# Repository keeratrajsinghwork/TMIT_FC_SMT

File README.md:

# TMIT_FC_SMT
 SMT based flight computer created for thrustMIT

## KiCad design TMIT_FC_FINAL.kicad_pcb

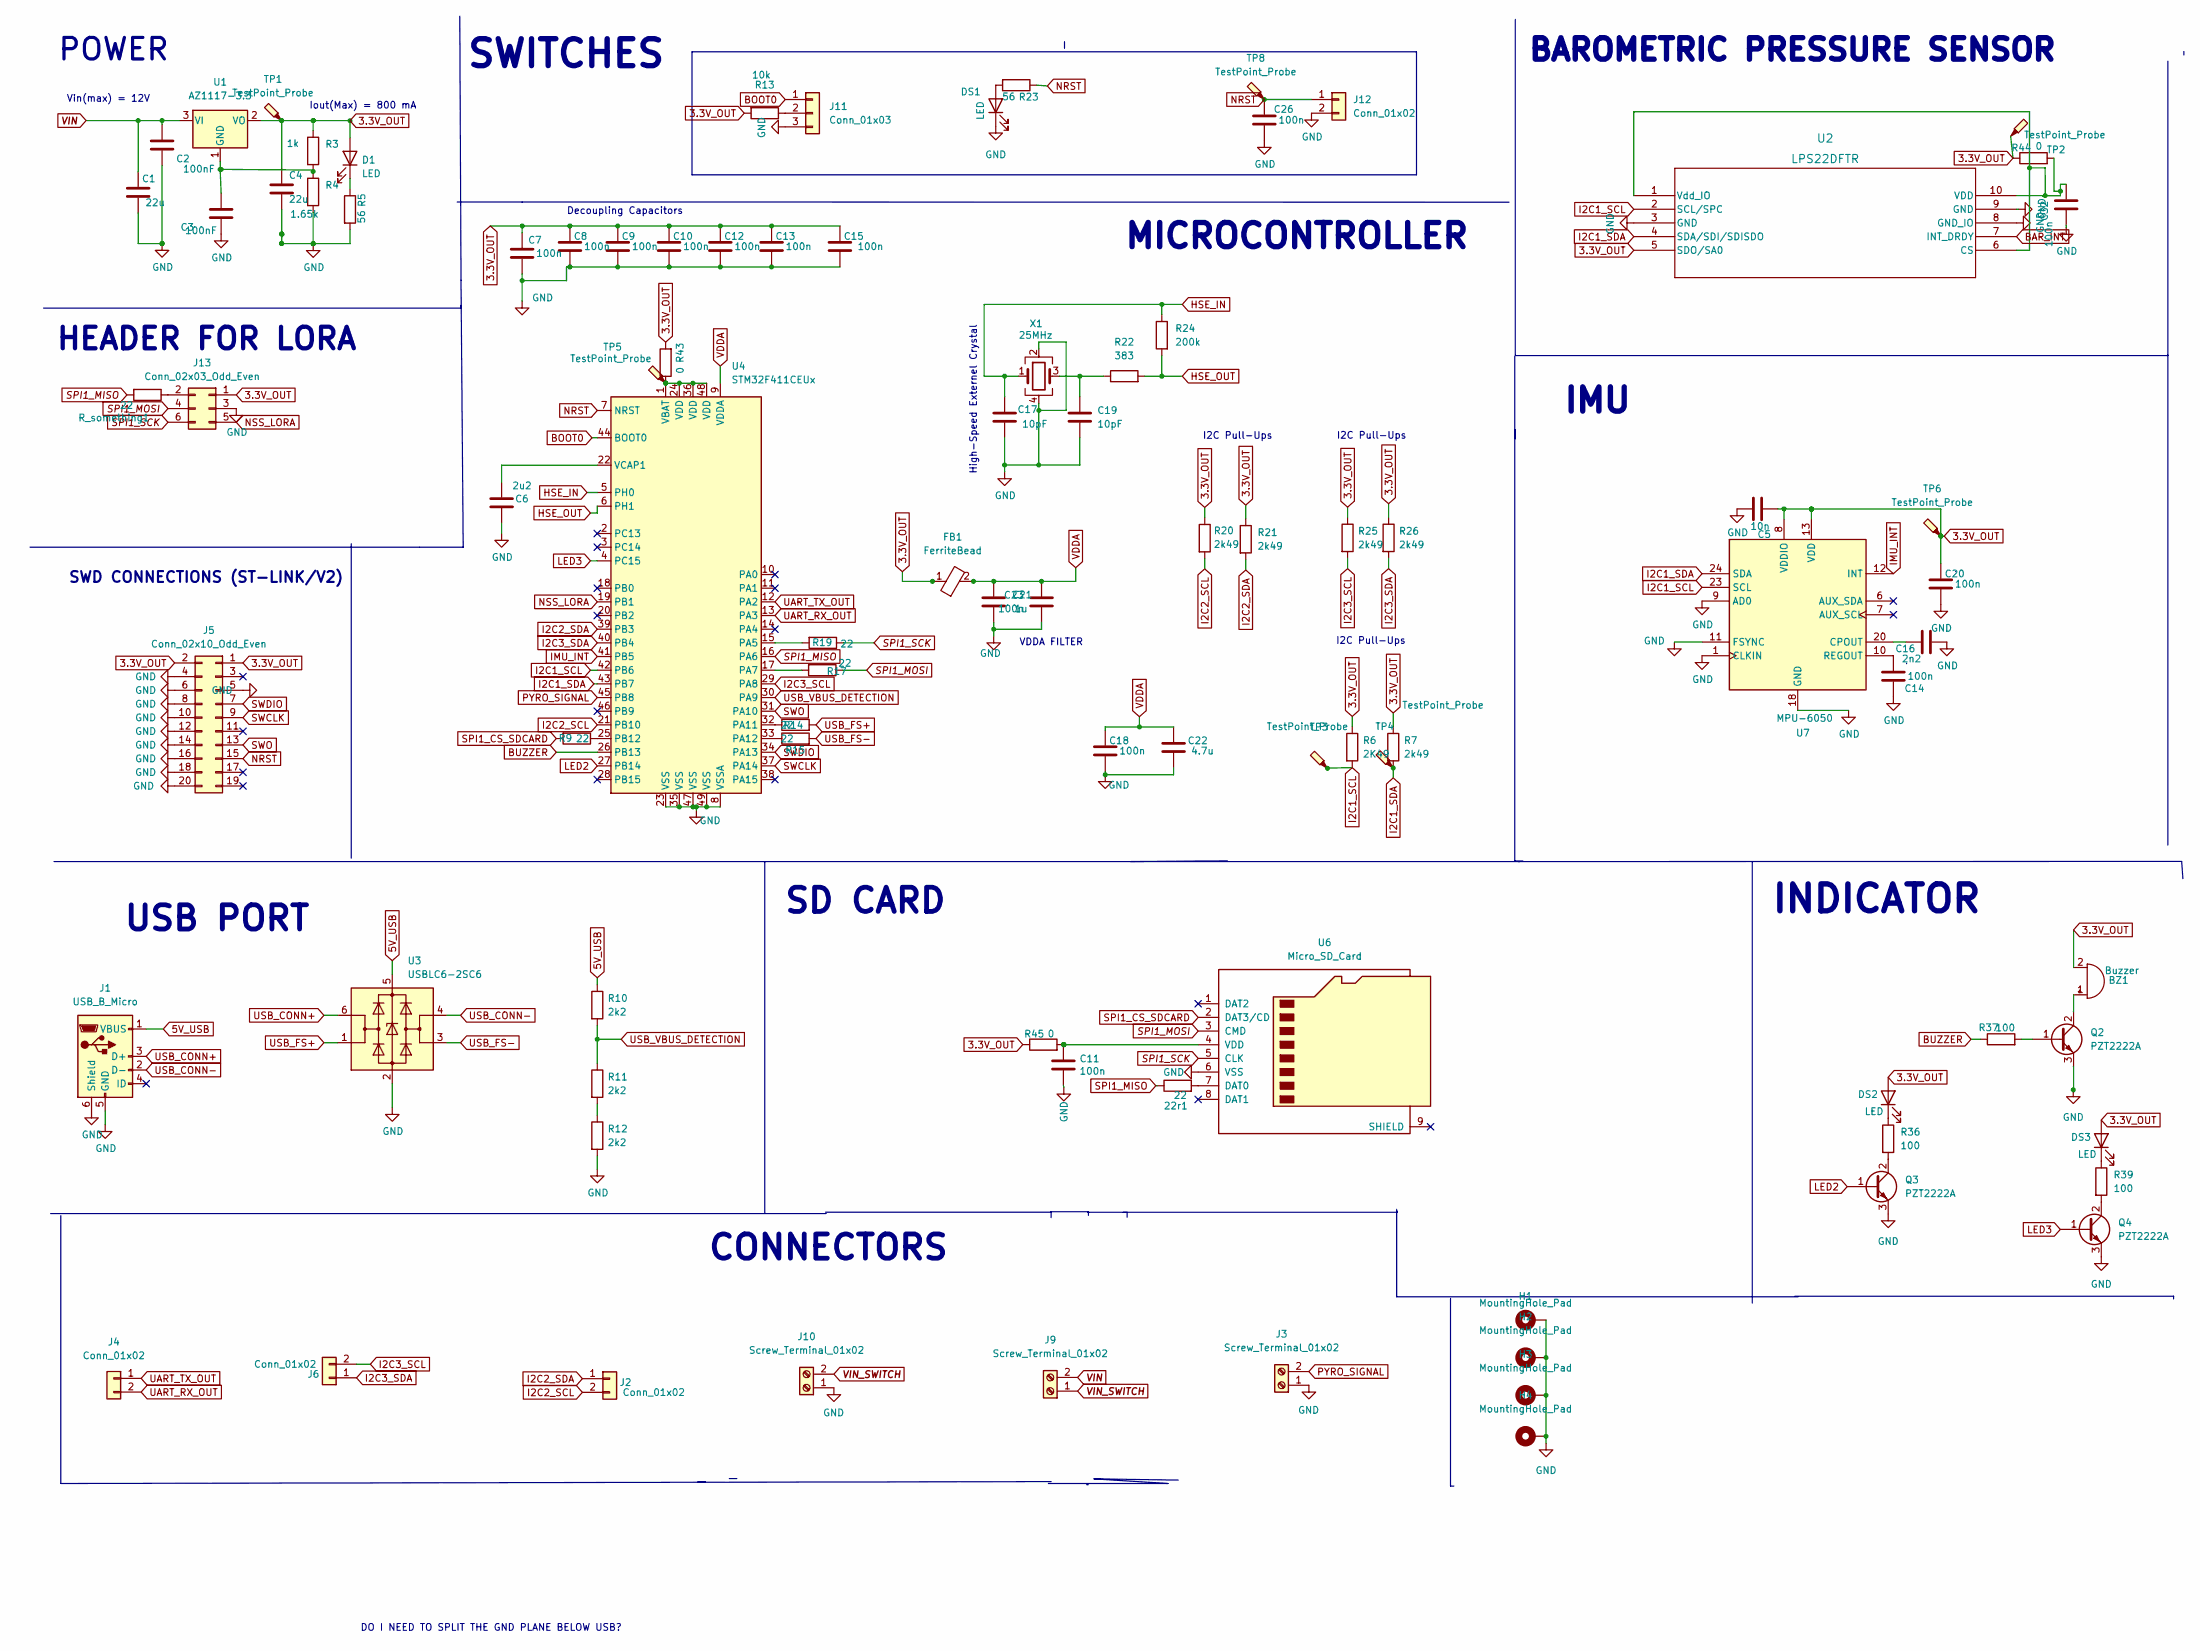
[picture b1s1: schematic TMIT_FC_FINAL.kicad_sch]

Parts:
22r1: 22; R_0603_1608Metric
BZ1: Buzzer; PinHeader_1x02_P2.54mm_Vertical
C1, C4: 22u; C_1206_3216Metric
C2, C3: 100nF; C_1206_3216Metric
C5: 10n; C_0805_2012Metric
C6: 2u2; C_1206_3216Metric
C7, C8, C9, C10, C11, C12, C13, C15, C18, C23, C26, C32: 100n; C_1206_3216Metric
C14, C20: 100n; C_0603_1608Metric
C16: 2n2; C_0805_2012Metric
C17, C19: 10pF; C_1206_3216Metric
C21: 1u; C_1206_3216Metric
C22: 4.7u; C_1206_3216Metric
D1: LED; LED_0805_2012Metric
DS1, DS2, DS3: LED; LED_0805_2012Metric
FB1: FerriteBead; L_0805_2012Metric
H1, H2, H3, H4: MountingHole_Pad; MountingHole_3.2mm_M3_Pad
J1: USB_B_Micro; USB_Micro-B_Molex-105133-0001
J2, J4, J6, J12: Conn_01x02; TerminalBlock_bornier-2_P5.08mm
J3, J9, J10: Screw_Terminal_01x02; TerminalBlock_bornier-2_P5.08mm
J5: Conn_02x10_Odd_Even; PinHeader_2x10_P2.54mm_Vertical
J11: Conn_01x03; TerminalBlock_bornier-3_P5.08mm
J13: Conn_02x03_Odd_Even; PinSocket_2x03_P2.54mm_Vertical
Q2, Q3, Q4: PZT2222A; SOT-223-3_TabPin2
R3: 1k; R_1206_3216Metric
R4: 1.65k; R_1206_3216Metric
R5, R23: 56; R_1206_3216Metric
R6: 2K49; R_1206_3216Metric
R7, R20, R21, R25, R26: 2k49; R_1206_3216Metric
R9, R14, R15, R17, R19: 22; R_1206_3216Metric
R10, R11, R12: 2k2; R_1206_3216Metric
R13: 10k; R_1206_3216Metric
R22: 383; R_1206_3216Metric
R24: 200k; R_1206_3216Metric
R36, R37, R39: 100; R_1206_3216Metric
R43, R44, R45: 0; R_1206_3216Metric
R_something1: 22; R_0603_1608Metric
TP1, TP2, TP3, TP4, TP5, TP6, TP8: TestPoint_Probe; TestPoint_Pad_2.0x2.0mm
U1: AZ1117-3.3; SOT-223-3_TabPin2
U2: LPS22DFTR; QFN_22DFTR_STM
U3: USBLC6-2SC6; SOT-23-6
U4: STM32F411CEUx; QFN-48-1EP_7x7mm_P0.5mm_EP5.6x5.6mm
U6: Micro_SD_Card; Micro_SD
U7: MPU-6050; InvenSense_QFN-24_4x4mm_P0.5mm
X1: 25MHz; Crystal_SMD_Abracon_ABM8G-4Pin_3.2x2.5mm

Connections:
3.3V_OUT: BZ1.2 (+), C4.1, C5.2, C7.1, C8.1, C9.1, C10.1, C12.1, C13.1, C15.1, C20.1, D1.2 (A), DS2.2 (A), DS3.2 (A), FB1.1, J5.1, J5.2, J13.1, R3.1, R6.1, R7.1, R13.2, R20.1, R21.1, R25.1, R26.1, R43.2, R44.1, R45.1, TP1.1, TP2.1, TP6.1, U1.2 (VO), U2.5 (SDO/SA0), U7.8 (VDDIO), U7.13 (VDD)
5V_USB: J1.1 (VBUS), R10.1, U3.5 (VBUS)
BAR_INT: U2.7 (INT_DRDY)
BOOT0: J11.1, U4.44 (BOOT0)
BUZZER: R37.1, U4.26 (PB13)
GND: C3.2, C5.1, C6.2, C7.2, C8.2, C9.2, C10.2, C11.2, C12.2, C13.2, C14.2, C15.2, C16.1, C17.2, C18.2, C19.2, C20.2, C21.2, C22.2, C23.2, C26.2, C32.2, DS1.1 (K), H1.1, H2.1, H3.1, H4.1, J1.5 (GND), J1.6 (Shield), J3.1, J5.4, J5.5, J5.6, J5.8, J5.10, J5.12, J5.14, J5.16, J5.18, J5.20, J10.1, J11.3, J12.2, J13.3, Q2.3 (E), Q3.3 (E), Q4.3 (E), R12.2, U2.3 (GND), U2.8 (GND_IO), U2.9 (GND), U3.2 (GND), U4.8 (VSSA), U4.23 (VSS), U4.35 (VSS), U4.47 (VSS), U4.49 (VSS), U6.6 (VSS), U7.1 (CLKIN), U7.9 (AD0), U7.11 (FSYNC), U7.18 (GND), X1.2, X1.4
HSE_IN: C17.1, R24.1, U4.5 (PH0), X1.1
HSE_OUT: R22.2, R24.2, U4.6 (PH1)
I2C1_SCL: R6.2, TP3.1, U2.2 (SCL/SPC), U4.42 (PB6), U7.23 (SCL)
I2C1_SDA: R7.2, TP4.1, U2.4 (SDA/SDI/SDISDO), U4.43 (PB7), U7.24 (SDA)
I2C2_SCL: J2.2, R20.2, U4.21 (PB10)
I2C2_SDA: J2.1, R21.2, U4.39 (PB3)
I2C3_SCL: J6.2, R25.2, U4.29 (PA8)
I2C3_SDA: J6.1, R26.2, U4.40 (PB4)
IMU_INT: U4.41 (PB5), U7.12 (INT)
LED2: Q3.1 (B), U4.27 (PB14)
LED3: Q4.1 (B), U4.4 (PC15)
NRST: C26.1, J5.15, J12.1, R23.1, TP8.1, U4.7 (NRST)
NSS_LORA: J13.5, U4.19 (PB1)
unnamed: 22r1.2, U6.7 (DAT0)
unnamed: BZ1.1 (-), Q2.2 (C)
unnamed: C1.2, C2.2
unnamed: C3.1, R3.2, R4.1, U1.1 (GND)
unnamed: C4.2, R4.2, R5.2
unnamed: C6.1, U4.22 (VCAP1)
unnamed: C11.1, R45.2, U6.4 (VDD)
unnamed: C14.1, U7.10 (REGOUT)
unnamed: C16.2, U7.20 (CPOUT)
unnamed: C19.1, R22.1, X1.3
unnamed: C32.1, R44.2, U2.1 (Vdd_IO), U2.6 (CS), U2.10 (VDD)
unnamed: D1.1 (K), R5.1
unnamed: DS1.2 (A), R23.2
unnamed: DS2.1 (K), R36.1
unnamed: DS3.1 (K), R39.1
unnamed: J11.2, R13.1
unnamed: J13.2, R_something1.1
unnamed: Q2.1 (B), R37.2
unnamed: Q3.2 (C), R36.2
unnamed: Q4.2 (C), R39.2
unnamed: R9.1, U4.25 (PB12)
unnamed: R11.2, R12.1
unnamed: R14.1, U4.32 (PA11)
unnamed: R15.1, U4.33 (PA12)
unnamed: R17.2, U4.17 (PA7)
unnamed: R19.2, U4.15 (PA5)
unnamed: R43.1, TP5.1, U4.1 (VBAT), U4.24 (VDD), U4.36 (VDD), U4.48 (VDD)
PYRO_SIGNAL: J3.2, U4.45 (PB8)
SPI1_CS_SDCARD: R9.2, U6.2 (DAT3/CD)
SPI1_MISO: 22r1.1, R_something1.2, U4.16 (PA6)
SPI1_MOSI: J13.4, R17.1, U6.3 (CMD)
SPI1_SCK: J13.6, R19.1, U6.5 (CLK)
SWCLK: J5.9, U4.37 (PA14)
SWDIO: J5.7, U4.34 (PA13)
SWO: J5.13, U4.31 (PA10)
UART_RX_OUT: J4.2, U4.13 (PA3)
UART_TX_OUT: J4.1, U4.12 (PA2)
USB_CONN+: J1.3 (D+), U3.6 (I/O1)
USB_CONN-: J1.2 (D-), U3.4 (I/O2)
USB_FS+: R14.2, U3.1 (I/O1)
USB_FS-: R15.2, U3.3 (I/O2)
USB_VBUS_DETECTION: R10.2, R11.1, U4.30 (PA9)
VDDA: C18.1, C21.1, C22.1, C23.1, FB1.2, U4.9 (VDDA)
VIN: C1.1, C2.1, J9.2, U1.3 (VI)
VIN_SWITCH: J9.1, J10.2

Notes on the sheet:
High-Speed Externel Crystal
SWD CONNECTIONS (ST-LINK/V2)
I2C Pull-Ups
MICROCONTROLLER
CONNECTORS
Vin(max) = 12V
IMU
SD CARD
DO I NEED TO SPLIT THE GND PLANE BELOW USB?
Iout(Max) = 800 mA
BAROMETRIC PRESSURE SENSOR
USB PORT
Decoupling Capacitors
POWER
HEADER FOR LORA
INDICATOR
VDDA FILTER
SWITCHES

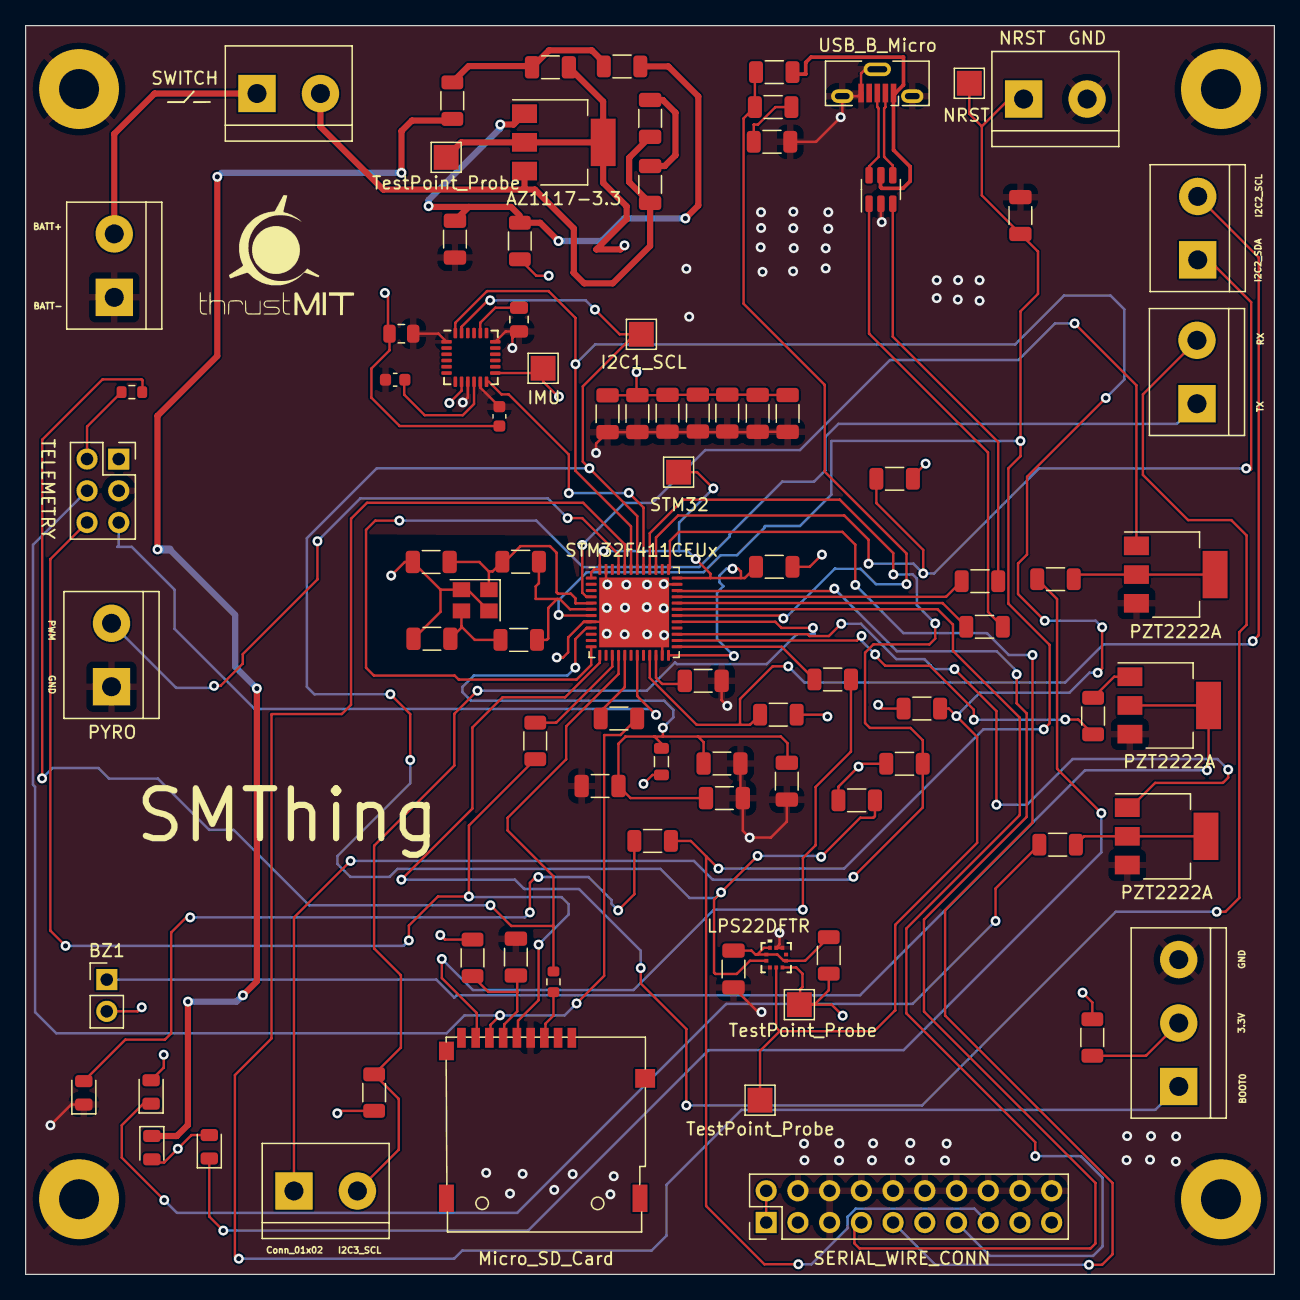
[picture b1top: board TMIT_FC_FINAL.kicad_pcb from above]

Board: 4 copper layers, 100.0 x 100.0 mm, 92 parts (0 on the bottom side), 63 nets.

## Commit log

2023-09-12 Backup files removed
